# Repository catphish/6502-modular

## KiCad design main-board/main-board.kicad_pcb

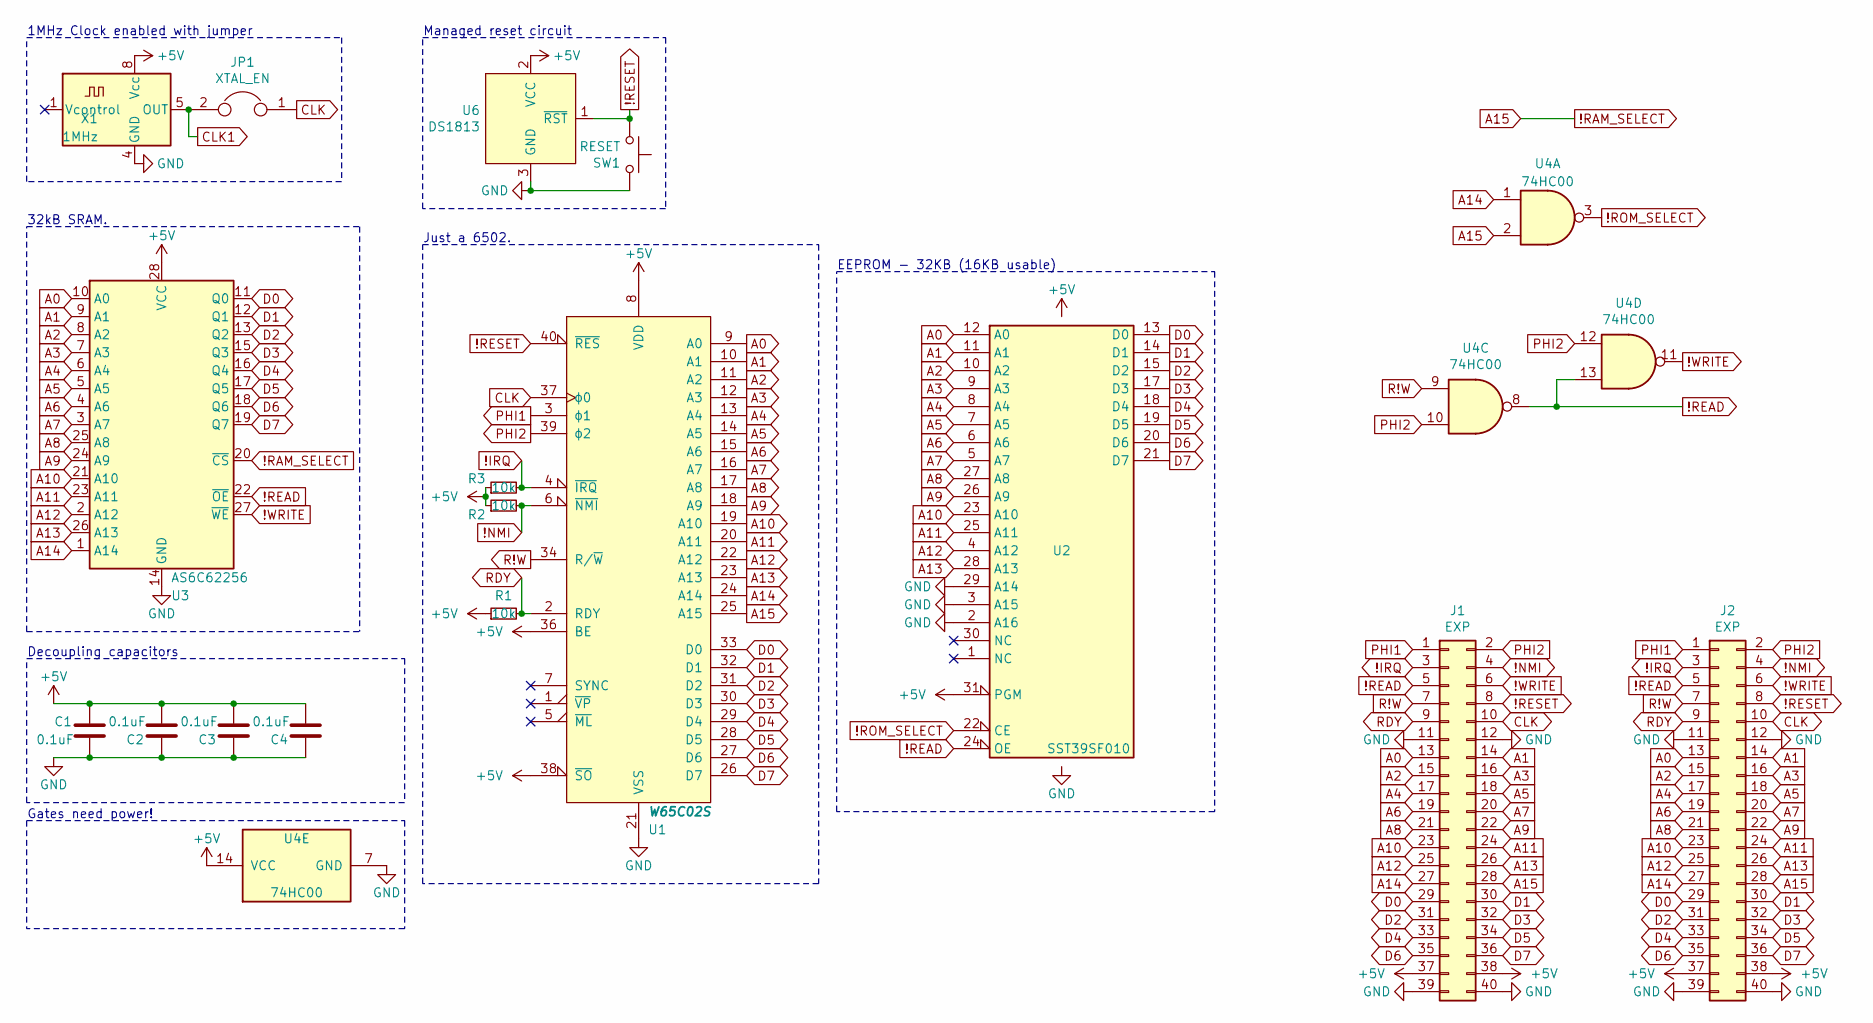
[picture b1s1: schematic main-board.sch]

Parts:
C1, C2, C3, C4: 0.1uF; C_Disc_D6.0mm_W2.5mm_P5.00mm
J1, J2: EXP; PinHeader_2x20_P2.54mm_Vertical
JP1: XTAL_EN; PinHeader_1x02_P2.54mm_Horizontal
R1, R2, R3: 10k; R_Axial_DIN0207_L6.3mm_D2.5mm_P10.16mm_Horizontal
SW1: RESET; SW_PUSH_6mm
U1: W65C02S; DIP-40_W15.24mm_Socket
U2: SST39SF010; DIP-32_W15.24mm_Socket
U3: AS6C62256; DIP-28_W15.24mm_Socket
U4: 74HC00; DIP-14_W7.62mm_Socket
U6: DS1813; TO-92_Inline_Horizontal1
X1: 1MHz; Oscillator_DIP-8

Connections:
!IRQ: J1.3, J2.3, R3.2, U1.4 (~IRQ)
!NMI: J1.4, J2.4, R2.2, U1.6 (~NMI)
!RAM_SELECT: J1.28, J2.28, U1.25 (A15), U3.20 (~CS), U4.2
!READ: J1.5, J2.5, U2.24 (OE), U3.22 (~OE), U4.8, U4.13
!RESET: J1.8, J2.8, SW1.1, U1.40 (~RES), U6.1 (~RST)
!ROM_SELECT: U2.22 (CE), U4.3
!WRITE: J1.6, J2.6, U3.27 (~WE), U4.11
+5V: C1.1, C2.2, C3.2, C4.2, J1.37, J1.38, J2.37, J2.38, R1.1, R2.1, R3.1, U1.8 (VDD), U1.36 (BE), U1.38 (~SO), U2.31 (PGM), U2.32 (VCC), U3.28 (VCC), U4.14 (VCC), U6.2 (VCC), X1.8 (Vcc)
A0: J1.13, J2.13, U1.9 (A0), U2.12 (A0), U3.10 (A0)
A1: J1.14, J2.14, U1.10 (A1), U2.11 (A1), U3.9 (A1)
A2: J1.15, J2.15, U1.11 (A2), U2.10 (A2), U3.8 (A2)
A3: J1.16, J2.16, U1.12 (A3), U2.9 (A3), U3.7 (A3)
A4: J1.17, J2.17, U1.13 (A4), U2.8 (A4), U3.6 (A4)
A5: J1.18, J2.18, U1.14 (A5), U2.7 (A5), U3.5 (A5)
A6: J1.19, J2.19, U1.15 (A6), U2.6 (A6), U3.4 (A6)
A7: J1.20, J2.20, U1.16 (A7), U2.5 (A7), U3.3 (A7)
A8: J1.21, J2.21, U1.17 (A8), U2.27 (A8), U3.25 (A8)
A9: J1.22, J2.22, U1.18 (A9), U2.26 (A9), U3.24 (A9)
A10: J1.23, J2.23, U1.19 (A10), U2.23 (A10), U3.21 (A10)
A11: J1.24, J2.24, U1.20 (A11), U2.25 (A11), U3.23 (A11)
A12: J1.25, J2.25, U1.22 (A12), U2.4 (A12), U3.2 (A12)
A13: J1.26, J2.26, U1.23 (A13), U2.28 (A13), U3.26 (A13)
A14: J1.27, J2.27, U1.24 (A14), U3.1 (A14), U4.1
CLK: J1.10, J2.10, JP1.1, U1.37 (ϕ0)
CLK1: JP1.2, X1.5 (OUT)
D0: J1.29, J2.29, U1.33 (D0), U2.13 (D0), U3.11 (Q0)
D1: J1.30, J2.30, U1.32 (D1), U2.14 (D1), U3.12 (Q1)
D2: J1.31, J2.31, U1.31 (D2), U2.15 (D2), U3.13 (Q2)
D3: J1.32, J2.32, U1.30 (D3), U2.17 (D3), U3.15 (Q3)
D4: J1.33, J2.33, U1.29 (D4), U2.18 (D4), U3.16 (Q4)
D5: J1.34, J2.34, U1.28 (D5), U2.19 (D5), U3.17 (Q5)
D6: J1.35, J2.35, U1.27 (D6), U2.20 (D6), U3.18 (Q6)
D7: J1.36, J2.36, U1.26 (D7), U2.21 (D7), U3.19 (Q7)
GND: C1.2, C2.1, C3.1, C4.1, J1.11, J1.12, J1.39, J1.40, J2.11, J2.12, J2.39, J2.40, SW1.2, U1.21 (VSS), U2.2 (A16), U2.3 (A15), U2.16 (GND), U2.29 (A14), U3.14 (GND), U4.7 (GND), U6.3 (GND), X1.4 (GND)
PHI1: J1.1, J2.1, U1.3 (ϕ1)
PHI2: J1.2, J2.2, U1.39 (ϕ2), U4.10, U4.12
R!W: J1.7, J2.7, U1.34 (R/~W), U4.9
RDY: J1.9, J2.9, R1.2, U1.2 (RDY)

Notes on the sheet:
32kB SRAM.
Gates need power!
1MHz Clock enabled with jumper
Decoupling capacitors
Just a 6502.
EEPROM - 32KB (16KB usable)
Managed reset circuit

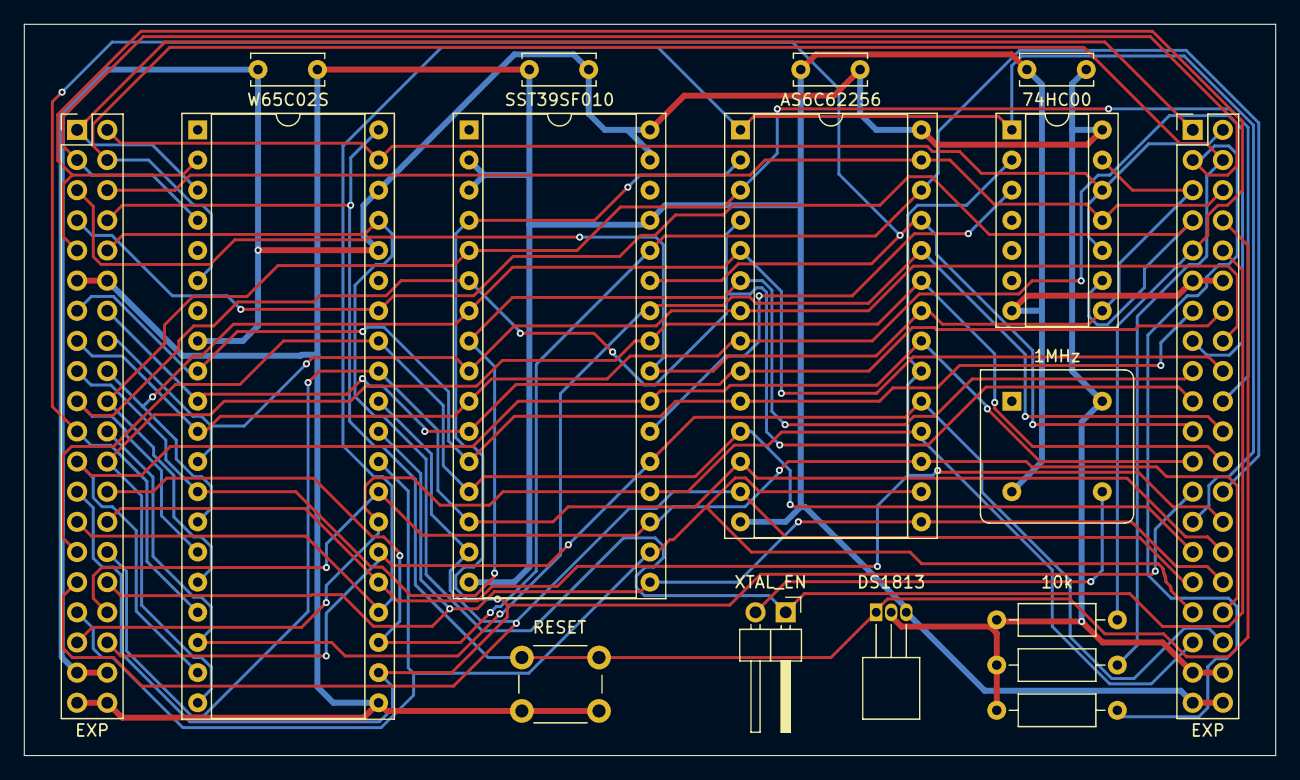
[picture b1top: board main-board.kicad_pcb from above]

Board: 2 copper layers, 105.4 x 61.6 mm, 17 parts (0 on the bottom side), 38 nets.

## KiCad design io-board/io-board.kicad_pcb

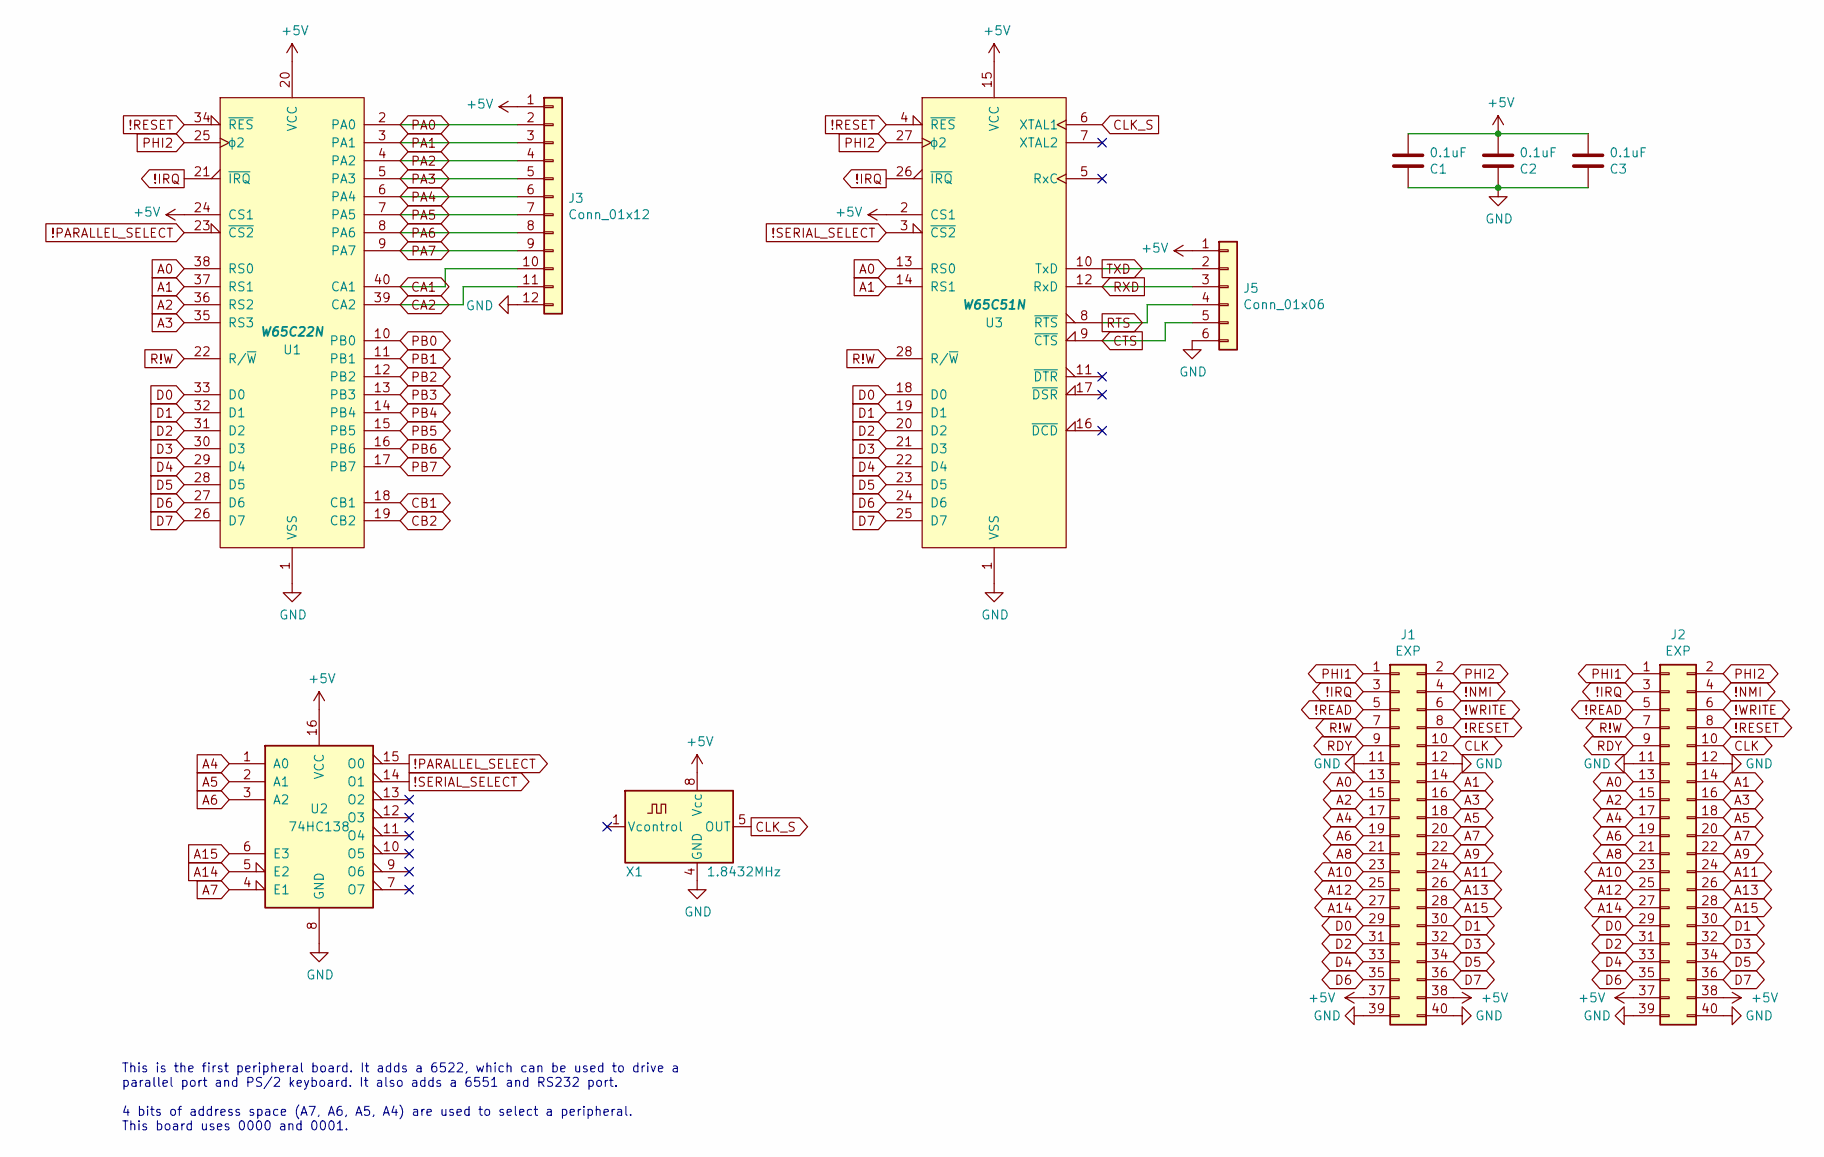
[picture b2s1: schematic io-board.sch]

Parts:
C1, C2, C3: 0.1uF; C_Disc_D6.0mm_W2.5mm_P5.00mm
J1, J2: EXP; PinHeader_2x20_P2.54mm_Vertical
J3: Conn_01x12; PinHeader_1x12_P2.54mm_Horizontal
J5: Conn_01x06; PinHeader_1x06_P2.54mm_Horizontal
U1: W65C22N; DIP-40_W15.24mm_Socket
U2: 74HC138; DIP-16_W7.62mm_Socket
U3: W65C51N; DIP-28_W15.24mm_Socket
X1: 1.8432MHz; Oscillator_DIP-8

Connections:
!IRQ: J1.3, J2.3, U1.21 (~IRQ), U3.26 (~IRQ)
!NMI: J1.4, J2.4
!PARALLEL_SELECT: U1.23 (~CS2), U2.15 (O0)
!READ: J1.5, J2.5
!RESET: J1.8, J2.8, U1.34 (~RES), U3.4 (~RES)
!SERIAL_SELECT: U2.14 (O1), U3.3 (~CS2)
!WRITE: J1.6, J2.6
+5V: C1.2, C2.2, C3.2, J1.37, J1.38, J2.37, J2.38, J3.1, J5.1, U1.20 (VCC), U1.24 (CS1), U2.16 (VCC), U3.2 (CS1), U3.15 (VCC), X1.8 (Vcc)
A0: J1.13, J2.13, U1.38 (RS0), U3.13 (RS0)
A1: J1.14, J2.14, U1.37 (RS1), U3.14 (RS1)
A2: J1.15, J2.15, U1.36 (RS2)
A3: J1.16, J2.16, U1.35 (RS3)
A4: J1.17, J2.17, U2.1 (A0)
A5: J1.18, J2.18, U2.2 (A1)
A6: J1.19, J2.19, U2.3 (A2)
A7: J1.20, J2.20, U2.4 (E1)
A8: J1.21, J2.21
A9: J1.22, J2.22
A10: J1.23, J2.23
A11: J1.24, J2.24
A12: J1.25, J2.25
A13: J1.26, J2.26
A14: J1.27, J2.27, U2.5 (E2)
A15: J1.28, J2.28, U2.6 (E3)
CA1: J3.10, U1.40 (CA1)
CA2: J3.11, U1.39 (CA2)
CB1: U1.18 (CB1)
CB2: U1.19 (CB2)
CLK: J1.10, J2.10
CLK_S: U3.6 (XTAL1), X1.5 (OUT)
CTS: J5.5, U3.9 (~CTS)
D0: J1.29, J2.29, U1.33 (D0), U3.18 (D0)
D1: J1.30, J2.30, U1.32 (D1), U3.19 (D1)
D2: J1.31, J2.31, U1.31 (D2), U3.20 (D2)
D3: J1.32, J2.32, U1.30 (D3), U3.21 (D3)
D4: J1.33, J2.33, U1.29 (D4), U3.22 (D4)
D5: J1.34, J2.34, U1.28 (D5), U3.23 (D5)
D6: J1.35, J2.35, U1.27 (D6), U3.24 (D6)
D7: J1.36, J2.36, U1.26 (D7), U3.25 (D7)
GND: C1.1, C2.1, C3.1, J1.11, J1.12, J1.39, J1.40, J2.11, J2.12, J2.39, J2.40, J3.12, J5.6, U1.1 (VSS), U2.8 (GND), U3.1 (VSS), X1.4 (GND)
PA0: J3.2, U1.2 (PA0)
PA1: J3.3, U1.3 (PA1)
PA2: J3.4, U1.4 (PA2)
PA3: J3.5, U1.5 (PA3)
PA4: J3.6, U1.6 (PA4)
PA5: J3.7, U1.7 (PA5)
PA6: J3.8, U1.8 (PA6)
PA7: J3.9, U1.9 (PA7)
PB0: U1.10 (PB0)
PB1: U1.11 (PB1)
PB2: U1.12 (PB2)
PB3: U1.13 (PB3)
PB4: U1.14 (PB4)
PB5: U1.15 (PB5)
PB6: U1.16 (PB6)
PB7: U1.17 (PB7)
PHI1: J1.1, J2.1
PHI2: J1.2, J2.2, U1.25 (ϕ2), U3.27 (ϕ2)
R!W: J1.7, J2.7, U1.22 (R/~W), U3.28 (R/~W)
RDY: J1.9, J2.9
RTS: J5.4, U3.8 (~RTS)
RXD: J5.3, U3.12 (RxD)
TXD: J5.2, U3.10 (TxD)

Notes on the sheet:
This is the first peripheral board. It adds a 6522, which can be used to drive a parallel port and PS/2 keyboard. It also adds a 6551 and RS232 port. 4 bits of address space (A7, A6, A5, A4) are used to select a peripheral. This board uses 0000 and 0001.

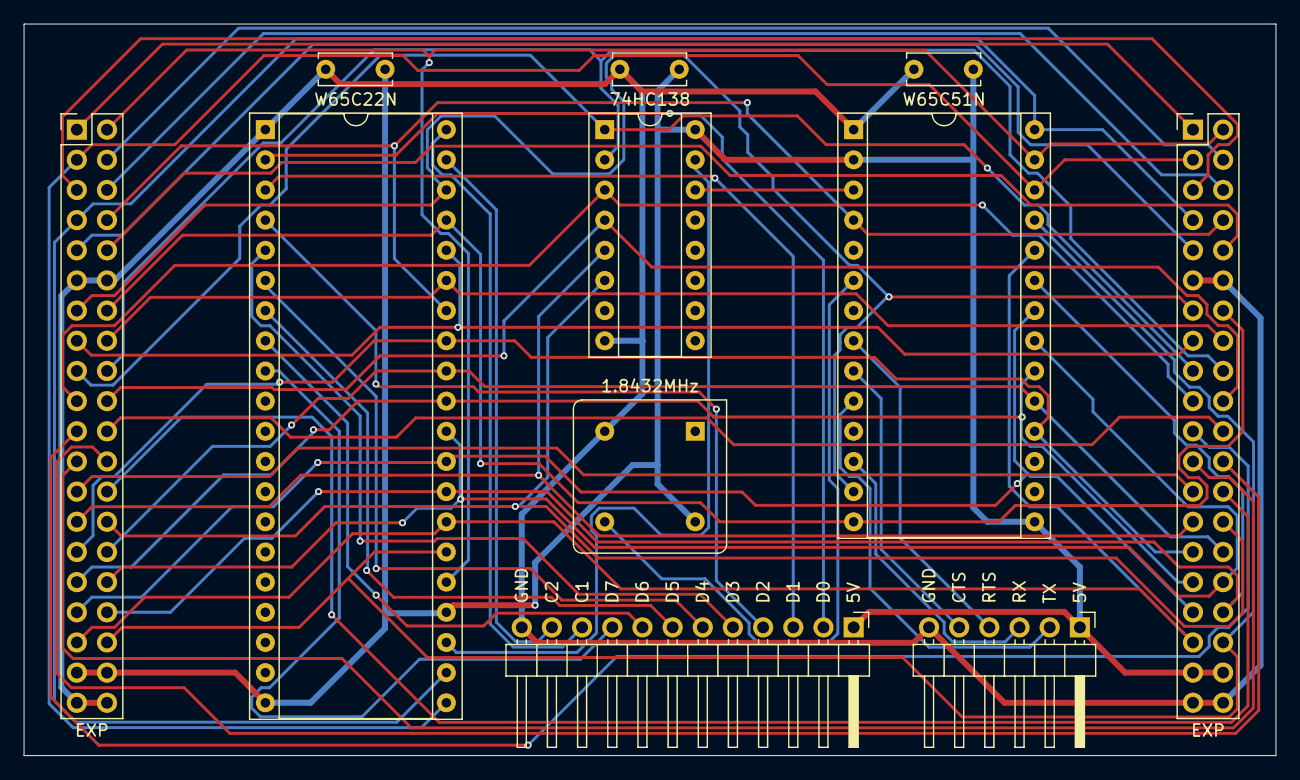
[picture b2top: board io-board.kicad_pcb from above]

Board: 2 copper layers, 105.4 x 61.6 mm, 11 parts (0 on the bottom side), 53 nets.

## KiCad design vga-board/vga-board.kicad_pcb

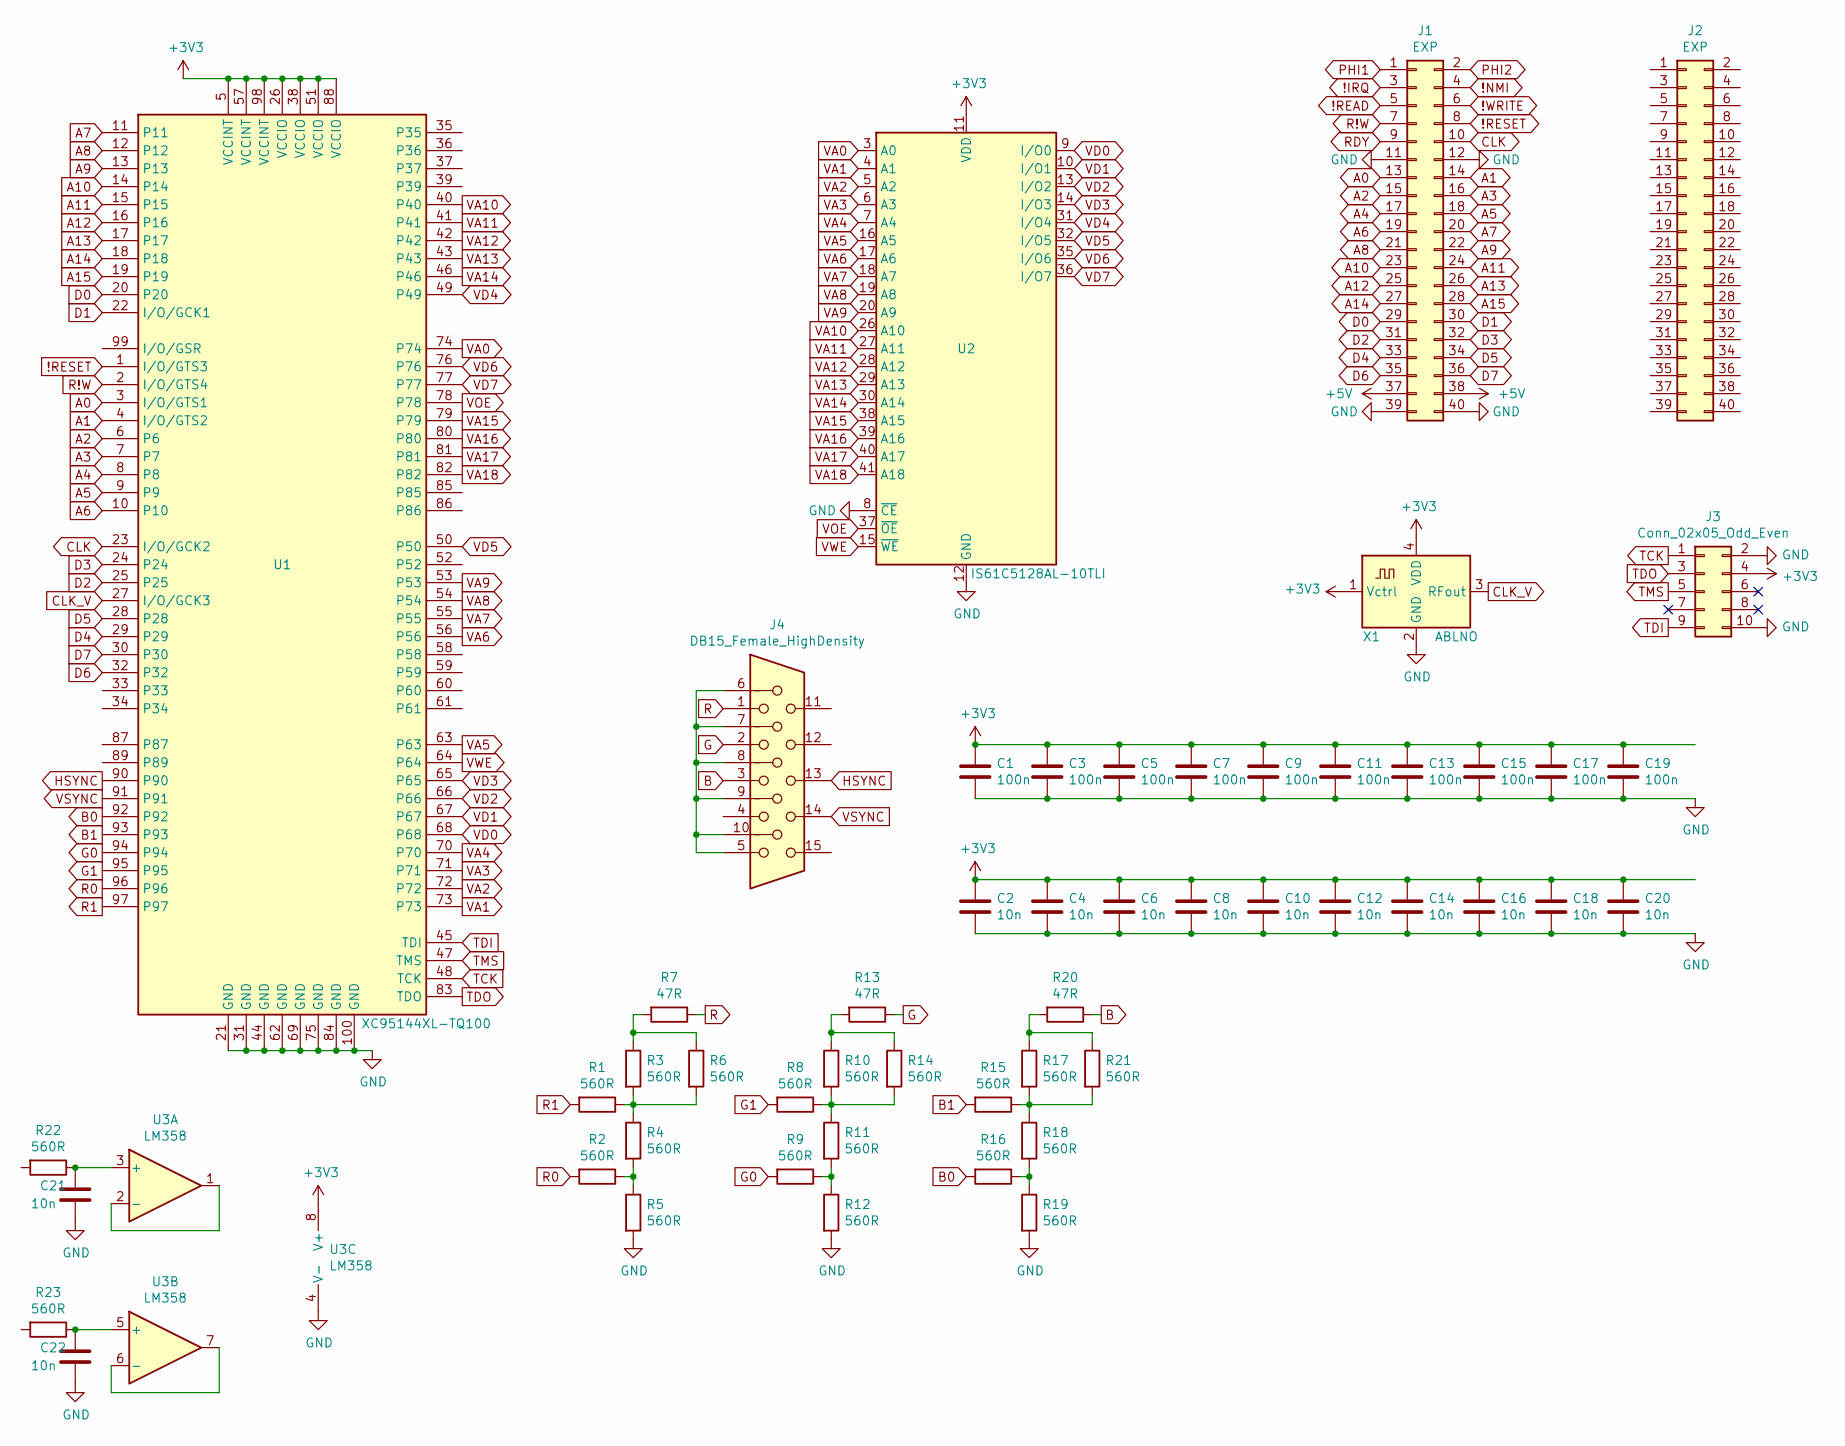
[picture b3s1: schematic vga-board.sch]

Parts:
C1, C3, C5, C7, C9, C11, C13, C15, C17, C19: 100n; C_0402_1005Metric
C2, C4, C6, C8, C10, C12, C14, C16, C18, C20, C21, C22: 10n; C_0402_1005Metric
J1, J2: EXP; PinHeader_2x20_P2.54mm_Vertical
J3: Conn_02x05_Odd_Even; IDC-Header_2x05_P2.54mm_Vertical
J4: DB15_Female_HighDensity; DSUB-15-HD_Female_Horizontal_P2.29x1.98mm_EdgePinOffset3.03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
R1, R2, R3, R4, R5, R6, R8, R9, R10, R11, R12, R14, R15, R16, R17, R18, R19, R21, R22, R23: 560R; R_0402_1005Metric
R7, R13, R20: 47R; R_0402_1005Metric
U1: XC95144XL-TQ100; TQFP-100_14x14mm_P0.5mm
U2: IS61C5128AL-10TLI; TSOP-II-44_10.16x18.41mm_P0.8mm
U3: LM358
X1: ABLNO; Oscillator_SMD_Abracon_ASV-4Pin_7.0x5.1mm

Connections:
!IRQ: J1.3
!NMI: J1.4
!READ: J1.5
!RESET: J1.8, U1.1 (I/O/GTS3)
!WRITE: J1.6
+3V3: C1.1, C2.1, C3.1, C4.1, C5.1, C6.1, C7.1, C8.1, C9.1, C10.1, C11.1, C12.1, C13.1, C14.1, C15.1, C16.1, C17.1, C18.1, C19.1, C20.1, J3.4, U1.5 (VCCINT), U1.26 (VCCIO), U1.38 (VCCIO), U1.51 (VCCIO), U1.57 (VCCINT), U1.88 (VCCIO), U1.98 (VCCINT), U2.11 (VDD), U2.33 (VDD), U3.8 (V+), X1.1 (Vctrl), X1.4 (VDD)
+5V: J1.37, J1.38
A0: J1.13, U1.3 (I/O/GTS1)
A1: J1.14, U1.4 (I/O/GTS2)
A2: J1.15, U1.6
A3: J1.16, U1.7
A4: J1.17, U1.8
A5: J1.18, U1.9
A6: J1.19, U1.10
A7: J1.20, U1.11
A8: J1.21, U1.12
A9: J1.22, U1.13
A10: J1.23, U1.14
A11: J1.24, U1.15
A12: J1.25, U1.16
A13: J1.26, U1.17
A14: J1.27, U1.18
A15: J1.28, U1.19
B: J4.3, R20.1
B0: R16.2, U1.92
B1: R15.2, U1.93
CLK: J1.10, U1.23 (I/O/GCK2)
CLK_V: U1.27 (I/O/GCK3), X1.3 (RFout)
D0: J1.29, U1.20
D1: J1.30, U1.22 (I/O/GCK1)
D2: J1.31, U1.25
D3: J1.32, U1.24
D4: J1.33, U1.29
D5: J1.34, U1.28
D6: J1.35, U1.32
D7: J1.36, U1.30
G: J4.2, R13.1
G0: R9.2, U1.94
G1: R8.2, U1.95
GND: C1.2, C2.2, C3.2, C4.2, C5.2, C6.2, C7.2, C8.2, C9.2, C10.2, C11.2, C12.2, C13.2, C14.2, C15.2, C16.2, C17.2, C18.2, C19.2, C20.2, C21.2, C22.2, J1.11, J1.12, J1.39, J1.40, J3.2, J3.10, R5.2, R12.2, R19.2, U1.21 (GND), U1.31 (GND), U1.44 (GND), U1.62 (GND), U1.69 (GND), U1.75 (GND), U1.84 (GND), U1.100 (GND), U2.8 (~CE), U2.12 (GND), U2.34 (GND), U3.4 (V-), X1.2 (GND)
HSYNC: J4.13, U1.90
unnamed: C21.1, R22.1, U3.3 (+)
unnamed: C22.1, R23.1, U3.5 (+)
unnamed: J4.5, J4.6, J4.7, J4.8, J4.9, J4.10
unnamed: R1.1, R3.2, R4.1, R6.2
unnamed: R2.1, R4.2, R5.1
unnamed: R3.1, R6.1, R7.2
unnamed: R10.1, R13.2, R14.1
unnamed: R8.1, R10.2, R11.1, R14.2
unnamed: R9.1, R11.2, R12.1
unnamed: R15.1, R17.2, R18.1, R21.2
unnamed: R16.1, R18.2, R19.1
unnamed: R17.1, R20.2, R21.1
unnamed: U3.1, U3.2 (-)
unnamed: U3.6 (-), U3.7
PHI1: J1.1
PHI2: J1.2
R: J4.1, R7.1
R0: R2.2, U1.96
R1: R1.2, U1.97
R!W: J1.7, U1.2 (I/O/GTS4)
RDY: J1.9
TCK: J3.1, U1.48 (TCK)
TDI: J3.9, U1.45 (TDI)
TDO: J3.3, U1.83 (TDO)
TMS: J3.5, U1.47 (TMS)
VA0: U1.74, U2.3 (A0)
VA1: U1.73, U2.4 (A1)
VA2: U1.72, U2.5 (A2)
VA3: U1.71, U2.6 (A3)
VA4: U1.70, U2.7 (A4)
VA5: U1.63, U2.16 (A5)
VA6: U1.56, U2.17 (A6)
VA7: U1.55, U2.18 (A7)
VA8: U1.54, U2.19 (A8)
VA9: U1.53, U2.20 (A9)
VA10: U1.40, U2.26 (A10)
VA11: U1.41, U2.27 (A11)
VA12: U1.42, U2.28 (A12)
VA13: U1.43, U2.29 (A13)
VA14: U1.46, U2.30 (A14)
VA15: U1.79, U2.38 (A15)
VA16: U1.80, U2.39 (A16)
VA17: U1.81, U2.40 (A17)
VA18: U1.82, U2.41 (A18)
VD0: U1.68, U2.9 (I/O0)
VD1: U1.67, U2.10 (I/O1)
VD2: U1.66, U2.13 (I/O2)
VD3: U1.65, U2.14 (I/O3)
VD4: U1.49, U2.31 (I/O4)
VD5: U1.50, U2.32 (I/O5)
VD6: U1.76, U2.35 (I/O6)
VD7: U1.77, U2.36 (I/O7)
VOE: U1.78, U2.37 (~OE)
VSYNC: J4.14, U1.91
VWE: U1.64, U2.15 (~WE)

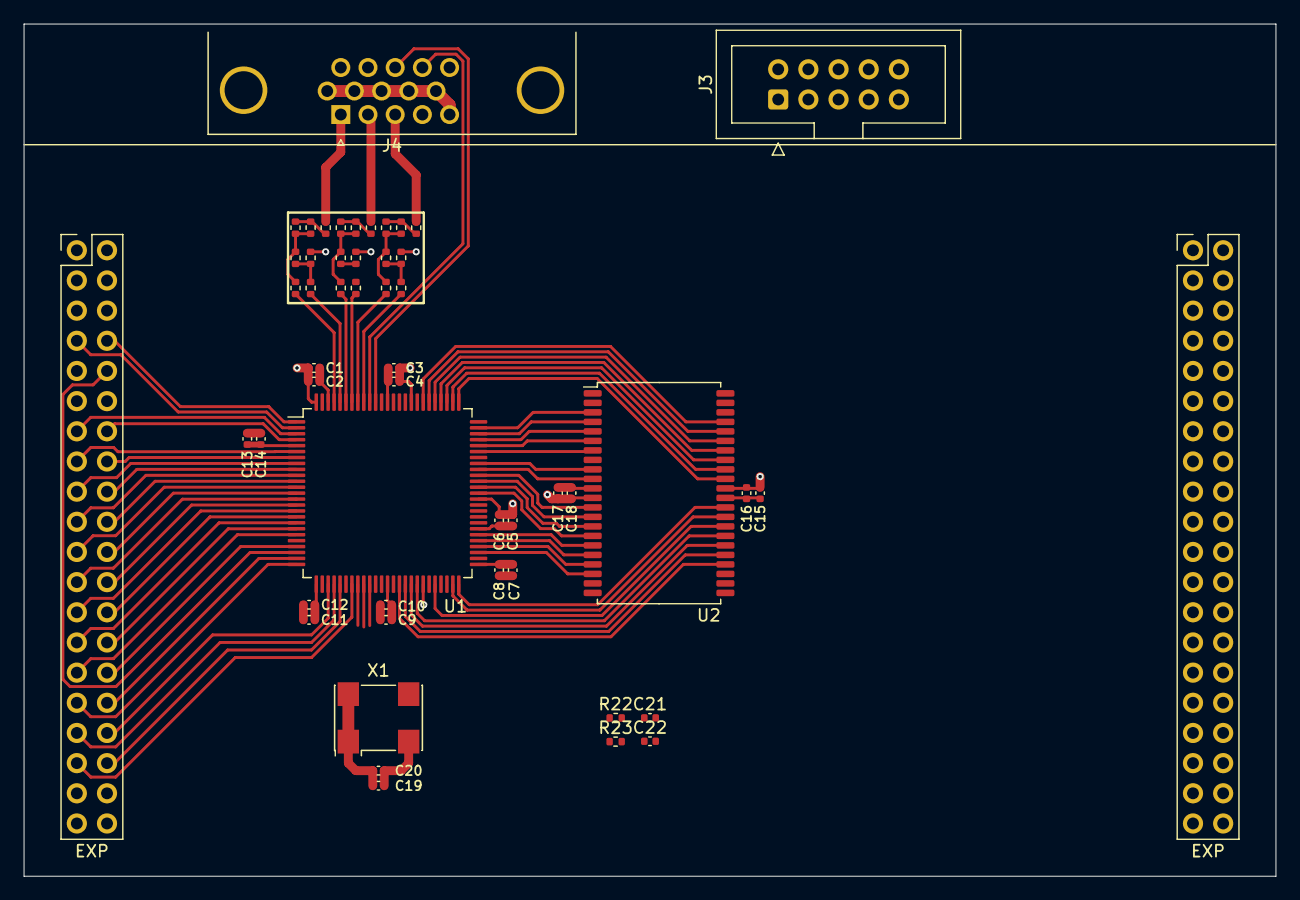
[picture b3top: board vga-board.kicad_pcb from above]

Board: 2 copper layers, 105.4 x 71.8 mm, 52 parts (0 on the bottom side), 87 nets.

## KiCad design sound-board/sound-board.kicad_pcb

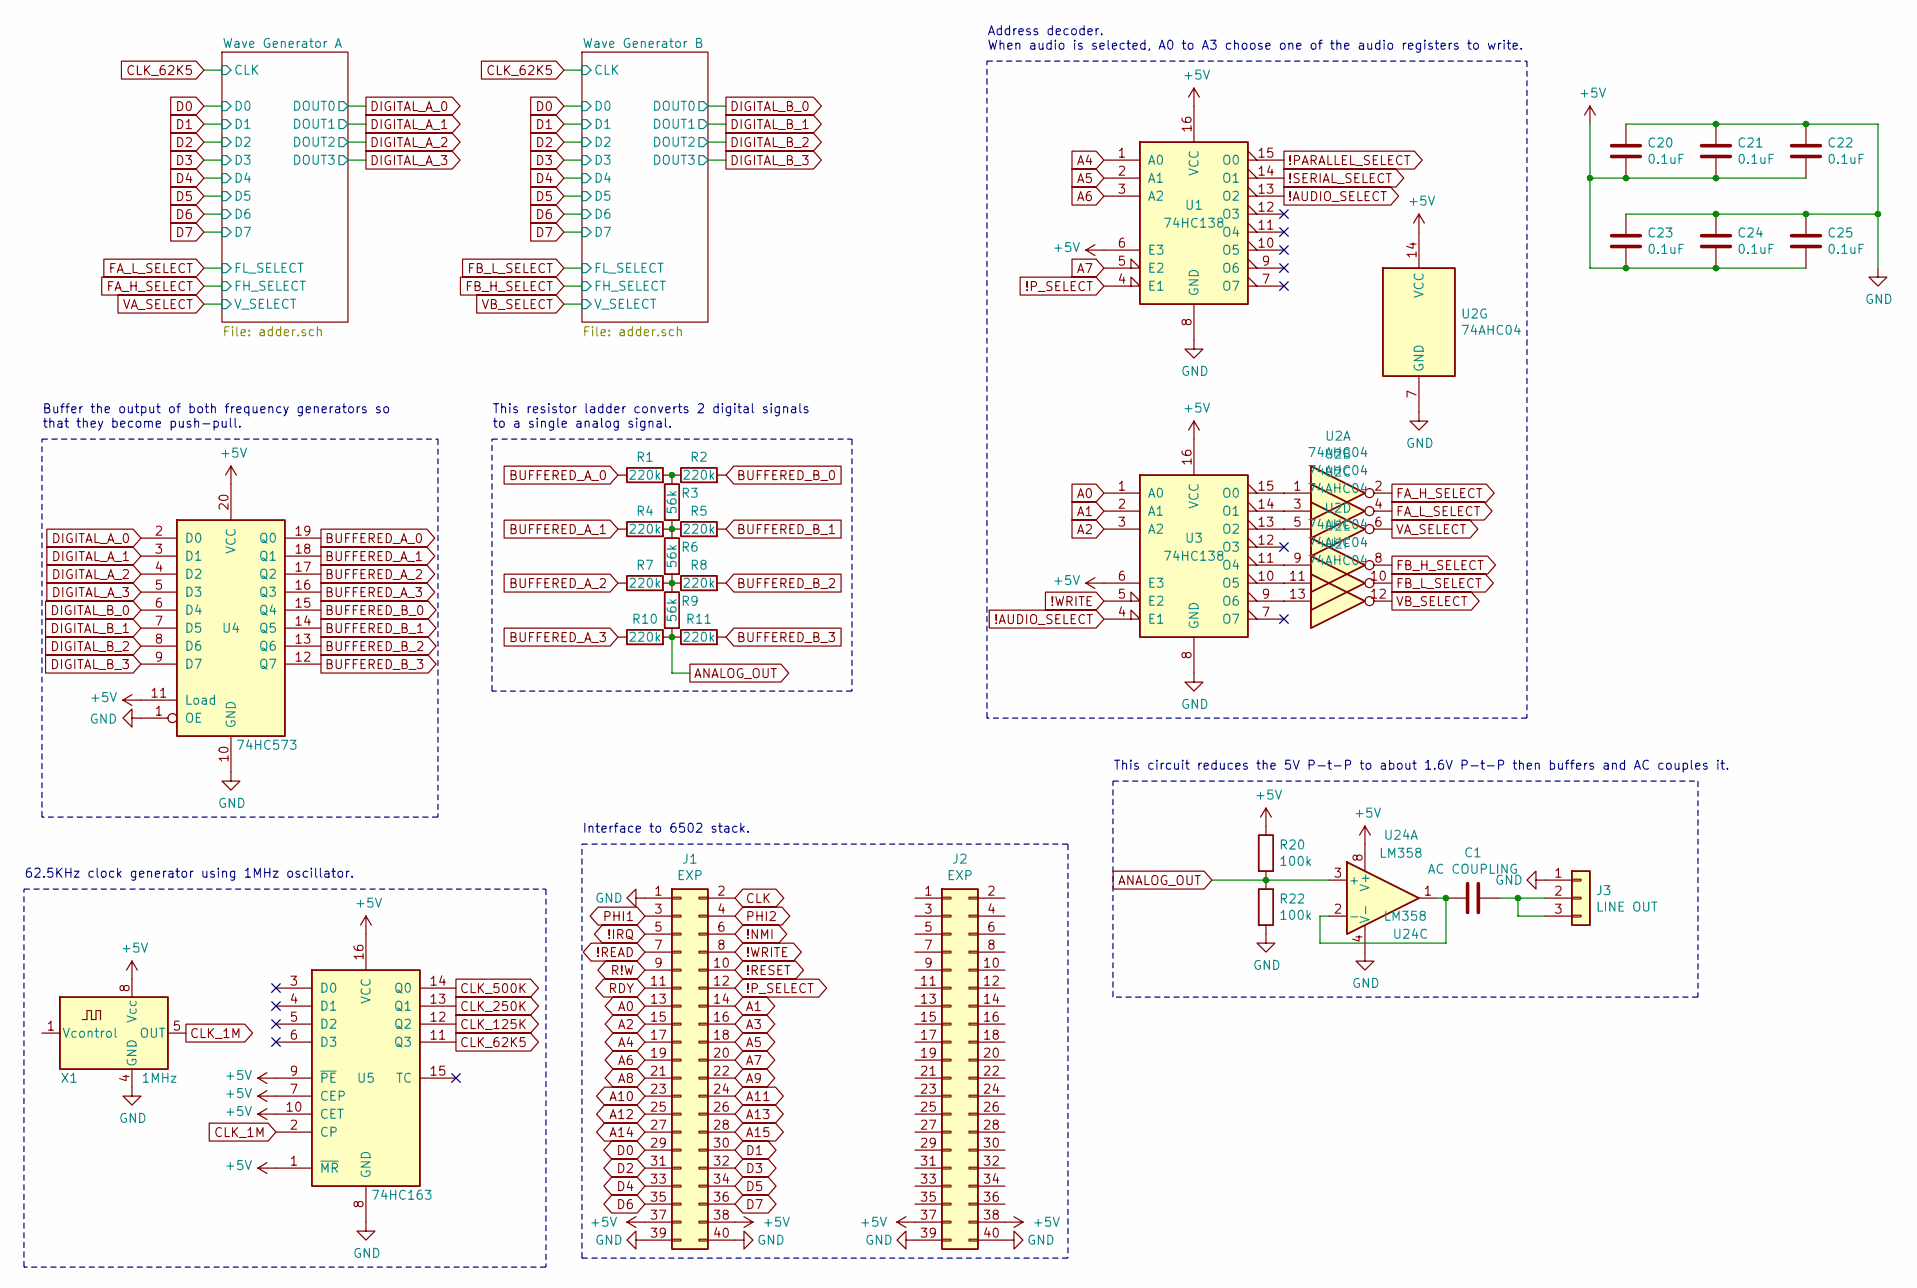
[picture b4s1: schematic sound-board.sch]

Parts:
C1: AC COUPLING; C_Disc_D6.0mm_W2.5mm_P5.00mm
C20, C21, C22, C23, C24, C25: 0.1uF; C_Disc_D6.0mm_W2.5mm_P5.00mm
J1, J2: EXP; PinHeader_2x20_P2.54mm_Vertical
J3: LINE OUT; SJ13523N
R1, R2, R4, R5, R7, R8, R10, R11: 220k; R_Axial_DIN0207_L6.3mm_D2.5mm_P10.16mm_Horizontal
R3, R6, R9: 56k; R_Axial_DIN0207_L6.3mm_D2.5mm_P10.16mm_Horizontal
R20, R22: 100k; R_Axial_DIN0207_L6.3mm_D2.5mm_P10.16mm_Horizontal
U1, U3: 74HC138; DIP-16_W7.62mm_Socket
U2: 74AHC04; DIP-14_W7.62mm_Socket
U4: 74HC573; DIP-20_W7.62mm_Socket
U5: 74HC163; DIP-16_W7.62mm_Socket
U24: LM358; DIP-8_W7.62mm_Socket
X1: 1MHz; Oscillator_DIP-8

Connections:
!AUDIO_SELECT: U1.13 (O2), U3.4 (E1)
!IRQ: J1.5
!NMI: J1.6
!PARALLEL_SELECT: U1.15 (O0)
!P_SELECT: J1.12, U1.4 (E1)
!READ: J1.7
!RESET: J1.10
!SERIAL_SELECT: U1.14 (O1)
!WRITE: J1.8, U3.5 (E2)
+5V: C20.2, C21.2, C22.2, C23.2, C24.2, C25.2, J1.37, J1.38, J2.37, J2.38, R20.1, U1.6 (E3), U1.16 (VCC), U2.14 (VCC), U3.6 (E3), U3.16 (VCC), U4.11 (Load), U4.20 (VCC), U5.1 (~MR), U5.7 (CEP), U5.9 (~PE), U5.10 (CET), U5.16 (VCC), U24.8 (V+), X1.8 (Vcc); also elsewhere on the board
A0: J1.13, U3.1 (A0)
A1: J1.14, U3.2 (A1)
A2: J1.15, U3.3 (A2)
A3: J1.16
A4: J1.17, U1.1 (A0)
A5: J1.18, U1.2 (A1)
A6: J1.19, U1.3 (A2)
A7: J1.20, U1.5 (E2)
A8: J1.21
A9: J1.22
A10: J1.23
A11: J1.24
A12: J1.25
A13: J1.26
A14: J1.27
A15: J1.28
ANALOG_OUT: R9.2, R10.2, R11.1, R20.2, R22.1, U24.3 (+)
BUFFERED_A_0: R1.1, U4.19 (Q0)
BUFFERED_A_1: R4.1, U4.18 (Q1)
BUFFERED_A_2: R7.1, U4.17 (Q2)
BUFFERED_A_3: R10.1, U4.16 (Q3)
BUFFERED_B_0: R2.2, U4.15 (Q4)
BUFFERED_B_1: R5.2, U4.14 (Q5)
BUFFERED_B_2: R8.2, U4.13 (Q6)
BUFFERED_B_3: R11.2, U4.12 (Q7)
CLK: J1.2
CLK_1M: U5.2 (CP), X1.5 (OUT)
CLK_62K5: U5.11 (Q3); also elsewhere on the board
CLK_125K: U5.12 (Q2)
CLK_250K: U5.13 (Q1)
CLK_500K: U5.14 (Q0)
D0: J1.29; also elsewhere on the board
D1: J1.30; also elsewhere on the board
D2: J1.31; also elsewhere on the board
D3: J1.32; also elsewhere on the board
D4: J1.33; also elsewhere on the board
D5: J1.34; also elsewhere on the board
D6: J1.35; also elsewhere on the board
D7: J1.36; also elsewhere on the board
DIGITAL_A_0: U4.2 (D0); also elsewhere on the board
DIGITAL_A_1: U4.3 (D1); also elsewhere on the board
DIGITAL_A_2: U4.4 (D2); also elsewhere on the board
DIGITAL_A_3: U4.5 (D3); also elsewhere on the board
DIGITAL_B_0: U4.6 (D4); also elsewhere on the board
DIGITAL_B_1: U4.7 (D5); also elsewhere on the board
DIGITAL_B_2: U4.8 (D6); also elsewhere on the board
DIGITAL_B_3: U4.9 (D7); also elsewhere on the board
FA_H_SELECT: U2.2; also elsewhere on the board
FA_L_SELECT: U2.4; also elsewhere on the board
FB_H_SELECT: U2.8; also elsewhere on the board
FB_L_SELECT: U2.10; also elsewhere on the board
GND: C20.1, C21.1, C22.1, C23.1, C24.1, C25.1, J1.1, J1.39, J1.40, J2.39, J2.40, J3.1, R22.2, U1.8 (GND), U2.7 (GND), U3.8 (GND), U4.1 (OE), U4.10 (GND), U5.8 (GND), U24.4 (V-), X1.4 (GND); also elsewhere on the board
unnamed: C1.1, J3.2, J3.3
unnamed: C1.2, U24.1, U24.2 (-)
unnamed: R1.2, R2.1, R3.1
unnamed: R3.2, R4.2, R5.1, R6.1
unnamed: R6.2, R7.2, R8.1, R9.1
unnamed: U2.1, U3.15 (O0)
unnamed: U2.3, U3.14 (O1)
unnamed: U2.5, U3.13 (O2)
unnamed: U2.9, U3.11 (O4)
unnamed: U2.11, U3.10 (O5)
unnamed: U2.13, U3.9 (O6)
PHI1: J1.3
PHI2: J1.4
R!W: J1.9
RDY: J1.11
VA_SELECT: U2.6; also elsewhere on the board
VB_SELECT: U2.12; also elsewhere on the board

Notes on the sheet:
Address decoder. When audio is selected, A0 to A3 choose one of the audio registers to write.
Buffer the output of both frequency generators so that they become push-pull.
This resistor ladder converts 2 digital signals to a single analog signal.
62.5KHz clock generator using 1MHz oscillator.
This circuit reduces the 5V P-t-P to about 1.6V P-t-P then buffers and AC couples it.
Interface to 6502 stack.
